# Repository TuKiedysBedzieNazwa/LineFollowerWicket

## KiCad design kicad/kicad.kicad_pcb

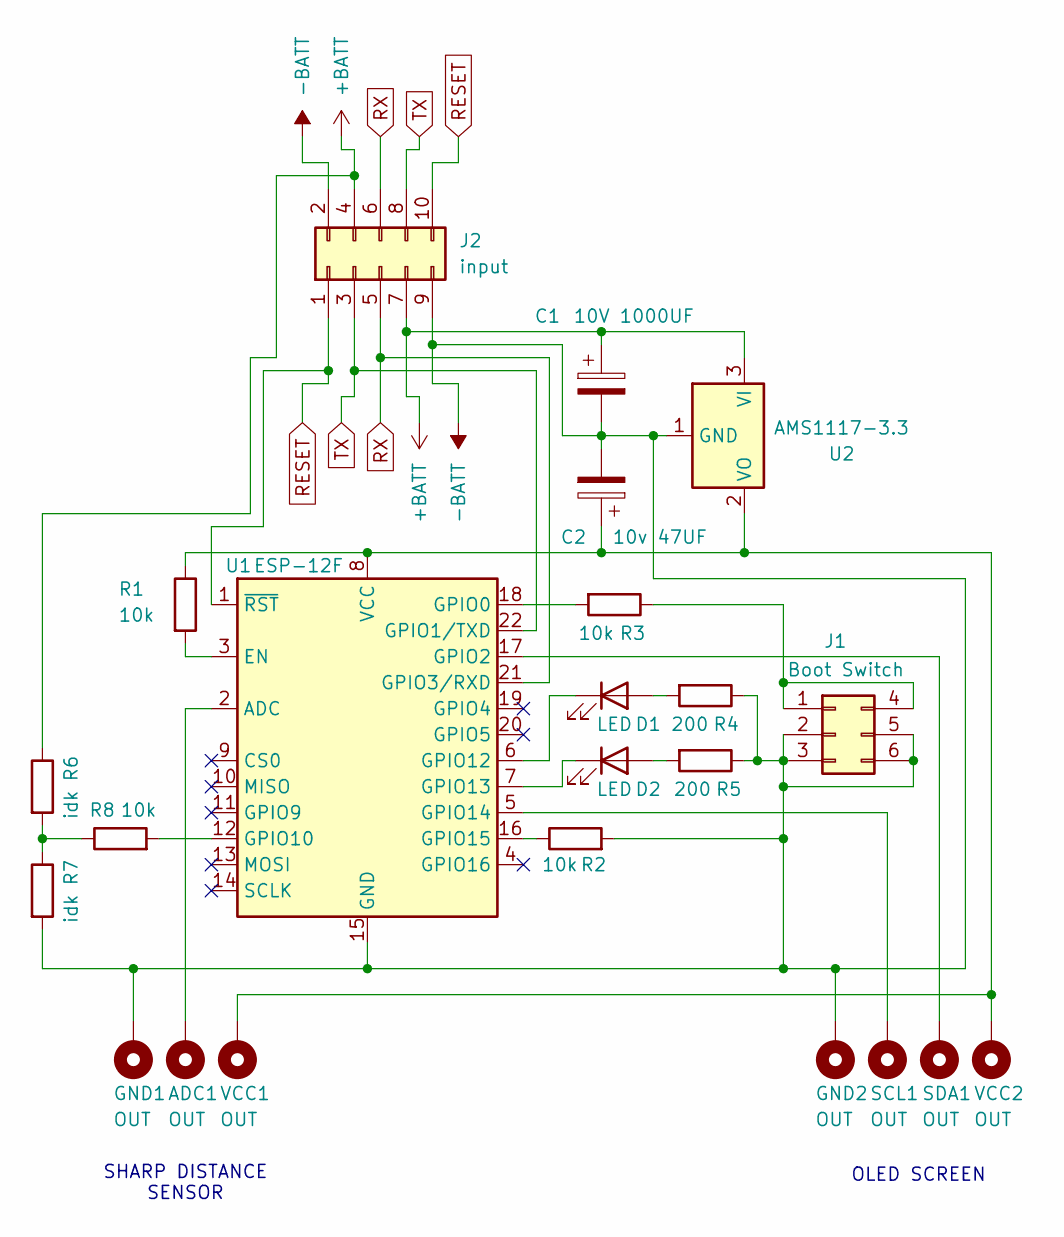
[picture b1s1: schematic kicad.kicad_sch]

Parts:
ADC1: OUT; TestPoint_Pad_2.0x2.0mm
C1: 10V 1000UF; CP_Radial_D8.0mm_P3.80mm
C2: 10v 47UF; CP_Radial_D4.0mm_P1.50mm
D1, D2: LED; LED_D5.0mm
GND1, GND2: OUT; TestPoint_Pad_2.0x2.0mm
J1: Boot Switch; PinHeader_2x03_P2.54mm_Vertical_SMD
J2: input; PinHeader_2x05_P2.54mm_Vertical_SMD
R1, R2, R3, R8: 10k; R_2512_6332Metric_Pad1.40x3.35mm_HandSolder
R4, R5: 200; R_2512_6332Metric_Pad1.40x3.35mm_HandSolder
R6, R7: idk; R_2512_6332Metric_Pad1.40x3.35mm_HandSolder
SCL1: OUT; TestPoint_Pad_2.0x2.0mm
SDA1: OUT; TestPoint_Pad_2.0x2.0mm
U1: ESP-12F; ESP-12E
U2: AMS1117-3.3; SOT-223-3_TabPin2
VCC1, VCC2: OUT; TestPoint_Pad_2.0x2.0mm

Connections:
+BATT: C1.1, J2.4, J2.7, R6.1, U2.3 (VI)
-BATT: C1.2, C2.2, GND1.1, GND2.1, J1.2, J1.3, J1.5, J1.6, J2.2, J2.9, R2.2, R4.1, R5.1, R7.2, U1.15 (GND), U2.1 (GND)
unnamed: D1.2 (A), R4.2
unnamed: D1.1 (K), U1.6 (GPIO12)
unnamed: D2.2 (A), R5.2
unnamed: D2.1 (K), U1.7 (GPIO13)
unnamed: J1.1, J1.4, R3.1
unnamed: R6.2, R7.1, R8.1
unnamed: ADC1.1, U1.2 (ADC)
unnamed: R1.2, U1.3 (EN)
unnamed: R3.2, U1.18 (GPIO0)
unnamed: SDA1.1, U1.17 (GPIO2)
unnamed: R8.2, U1.12 (GPIO10)
unnamed: SCL1.1, U1.5 (GPIO14)
unnamed: R2.1, U1.16 (GPIO15)
unnamed: C2.1, R1.1, U1.8 (VCC), U2.2 (VO), VCC1.1, VCC2.1
RESET: J2.1, J2.10, U1.1 (~RST)
RX: J2.5, J2.6, U1.21 (GPIO3/RXD)
TX: J2.3, J2.8, U1.22 (GPIO1/TXD)

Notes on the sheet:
SHARP DISTANCE SENSOR
OLED SCREEN

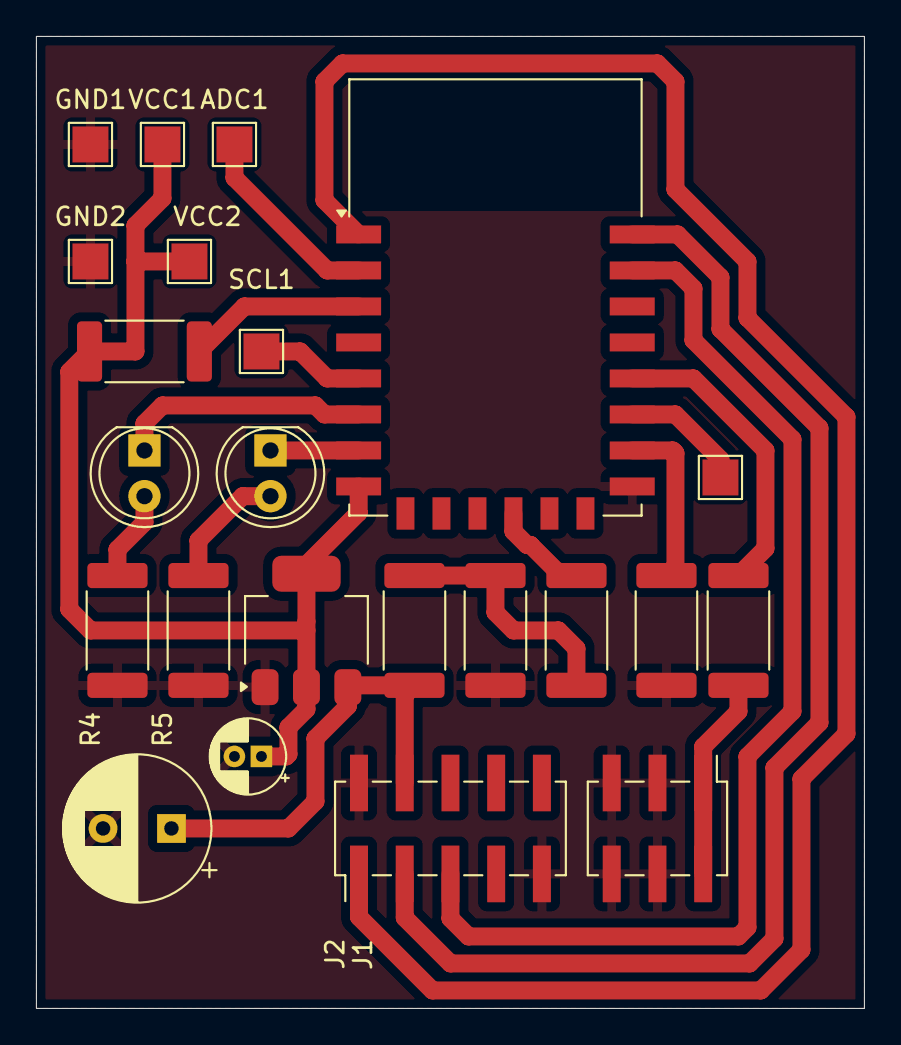
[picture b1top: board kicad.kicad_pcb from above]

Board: 2 copper layers, 46.0 x 54.0 mm, 23 parts (0 on the bottom side), 19 nets.

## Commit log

2024-10-27 POC: line follower wicket with one working sensor
2024-11-18 updated frontend backend, improved cpp, added admin panel
2024-11-19 build
2024-11-29 line follower competitions
